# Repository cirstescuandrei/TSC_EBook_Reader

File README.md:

# TSC_EBook_Reader

### Cîrstescu Andrei-Vlad 331CC

# Tabletă E-Paper ESP32-C6 – Documentație Hardware

## Descriere Generală

Această tabletă cu afișaj E-Paper este proiectată pentru consum redus de energie și uzabilitate extinsă. 
Se bazează pe ESP32-C6 și include funcționalități precum citire din microSD, senzori de mediu, RTC și 
interacțiune cu utilizatorul prin butoane tactile.

# BOM
| Components                                                                                                                                                                 	| Links                                                                                                                                                                         	|
|----------------------------------------------------------------------------------------------------------------------------------------------------------------------------	|-------------------------------------------------------------------------------------------------------------------------------------------------------------------------------	|
| BOOT_BUTTON, RESET_BUTTON, CANGE_BUTTON                                                                                                                                    	| https://industry.panasonic.com/global/en/products/control/switch/light-touch/number/evqpuj02k                                                                                 	|
| C1, C1_BAT, C1_BAT1, C1_BAT2, C2, C2_BAT, C4, C4_USB, C5, C6, C7, C8, C9, C10, C_DELAY,  EPD_C1, EPD_C2, EPD_C5, EPD_C6, EPD_C7, EPD_C8, EPD_C9, EPD_C10, EPD_C11, EPD_C12 	| https://componentsearchengine.com/part-view/CC0402MRX5R5BB106/YAGEO                                                                                                           	|
| C3                                                                                                                                                                         	| https://componentsearchengine.com/part-view/TCJB107M002R0055E/Kyocera%20AVX                                                                                                   	|
| C10_SUPERCAP                                                                                                                                                               	| https://www.snapeda.com/parts/CPH3225A/Seiko+Instruments/view-part/?ref=eda                                                                                                   	|
| CHG_LED                                                                                                                                                                    	| https://www.snapeda.com/parts/KP-1608SURCK/Kingbright/view-part/?ref=search&t=LED%200603                                                                                      	|
| D1                                                                                                                                                                         	| https://www.snapeda.com/parts/USBLC6-2SC6Y/STMicroelectronics/view-part/?ref=eda                                                                                              	|
| D2, D7                                                                                                                                                                     	| https://eu.mouser.com/ProductDetail/KYOCERA-AVX/SD0805S020S1R0?qs=jCA%252BPfw4LHbpkAoSnwrdjw%3D%3D                                                                            	|
| D3, D4, D5                                                                                                                                                                 	| https://www.snapeda.com/parts/MBR0530/Onsemi/view-part/?ref=eda                                                                                                               	|
| D6, D8, D9, D10, D11, D12                                                                                                                                                  	| https://www.snapeda.com/parts/PGB1010603MR/Littelfuse/view-part/?ref=eda                                                                                                      	|
| IC1                                                                                                                                                                        	| https://componentsearchengine.com/part-view/BD5229G-TR/ROHM%20Semiconductor                                                                                                   	|
| IC4                                                                                                                                                                        	| https://componentsearchengine.com/part-view/XC6220A331MR-G/Torex                                                                                                              	|
| J1                                                                                                                                                                         	| https://www.mouser.co.uk/ProductDetail/Hirose-Connector/FH34SRJ-24S-0.5SH99?qs=vcbW%252B4%252BSTIpKBl5ap9J8Fw%3D%3D                                                           	|
| J2                                                                                                                                                                         	| https://componentsearchengine.com/part-view/USB4110-GF-A/GCT%20(GLOBAL%20CONNECTOR%20TECHNOLOGY                                                                               	|
| J3                                                                                                                                                                         	| https://www.mouser.co.uk/ProductDetail/Adafruit/4208?qs=PzGy0jfpSMtbScLbr0L5dw%3D%3D                                                                                          	|
| J4                                                                                                                                                                         	| https://store.comet.srl.ro/Catalogue/Product/43497/                                                                                                                           	|
| L1                                                                                                                                                                         	| https://eu.mouser.com/ProductDetail/Wurth-Elektronik/744043680?qs=PGXP4M47uW6VkZq%252BkzjrHA%3D%3D                                                                            	|
| PFMF.050.1                                                                                                                                                                 	| https://www.mouser.co.uk/ProductDetail/EPCOS-TDK/B72520T0350K062?qs=dEfas%2FXlABIszF52uu7vrg%3D%3D                                                                            	|
| Q1, Q2                                                                                                                                                                     	| https://componentsearchengine.com/part-view/DMG2305UX-7/Diodes%20Incorporated                                                                                                 	|
| Q3                                                                                                                                                                         	| https://componentsearchengine.com/part-view/SI1308EDL-T1-GE3/Vishay_                                                                                                         	|
| R1, R1-PINH, R1-PINH1, R1_BAT, R1_PWRUSB, R2, R2-PINH, R2-PINH1, R2-USB, R2-USB1, R2_BAT, R3, R4, R5, R6, R7, R8, R9, 10, R_BOOT, R_CAPACITOR, R_CHANGE, R_CL1, R_RESET    	| https://componentsearchengine.com/part-view/R0402%201%25%20100%20K%20(RC0402FR-07100KL)/YAGEO                                                                                 	|
| SENSOR2                                                                                                                                                                    	| https://www.snapeda.com/parts/BME680/Bosch/view-part/?welcome=home                                                                                                            	|
| SJ1                                                                                                                                                                        	| https://grabcad.com/library/solder-jumpers-1                                                                                                                                  	|
| TP                                                                                                                                                                         	| -                                                                                                                                                                             	|
| U1                                                                                                                                                                         	| https://www.snapeda.com/parts/W25Q512JVEIQ/Winbond+Electronics/view-part/?ref=eda                                                                                             	|
| U2                                                                                                                                                                         	| https://www.snapeda.com/parts/ESP32-C6-WROOM-1-N8/Espressif+Systems/view-part/?ref=eda                                                                                        	|
| U3                                                                                                                                                                         	| https://www.snapeda.com/parts/DS3231SN%23/Analog+Devices/view-part/?ref=eda                                                                                                   	|
| U4                                                                                                                                                                         	| https://www.snapeda.com/parts/MAX17048G+T10/Analog+Devices/view-part/?ref=eda                                                                                                 	|
| U5                                                                                                                                                                         	| https://www.mouser.co.uk/ProductDetail/Microchip-Technology/MCP73831T-5ACI-OT?qs=hH%252BOa0VZEiAcgAcEkuamXg%3D%3D 	|

---

## Componente Principale

### ESP32-C6-WROOM-1-N8
- Control total: afișaj, senzori, memorie
- Protocoale: SPI, I²C, UART, USB 2.0
- Consum: ~130 mA activ / ~12 µA deep sleep

### Afișaj E-Paper 7.5” (800x480 px)
- SPI + GPIO: BUSY, DC, RST, CS
- Consum 0 mA idle, ~26 mA la refresh
- Perfect pentru afișare statică de lungă durată

### Memorie
- **W25Q512 NOR Flash** (64MB, SPI) – firmware & cărți
- **MicroSD Card** (SPI partajat) – fișiere externe

### RTC – DS3231SN
- I²C + GPIO (INT, RST)
- Timp real precis, funcțional și în sleep
- Suportă trezirea automată

### Senzor Ambiental – BME680
- Temperatură, umiditate, presiune, compuși volatili
- I²C partajat cu RTC
- Consum redus: ~2.1 mA activ

### Alimentare
- **Baterie Li-Po 2500 mAh**
- **Încărcare USB-C** cu MCP73831 (max 1A)
- **LDO XC6220** – 3.3V stabil pentru sistem
- Monitorizare baterie prin MAX17048 (ADC pe IO18)
- LED încărcare controlat de IO4

### USB-C & Protecție
- Protocol: USB 2.0 + VBUS
- Programare + alimentare
- Protecție ESD integrată

### Interfață Utilizator
- 3 butoane tactile: BOOT (IO15), RESET (IO3), CHANGE (IO23)
- LED stare încărcare (IO4)

### Extensii
- **Qwiic/Stemma QT**: senzori I²C plug & play (IO19/IO20)
- GPIO suplimentari disponibili

---

## Pinout ESP32-C6

| Pin ESP32 | Funcție       | Periferic           |
|-----------|---------------|---------------------|
| IO2       | MISO (SPI)    | Flash, SD, E-Paper  |
| IO6       | SCK (SPI)     | Flash, SD, E-Paper  |
| IO7       | MOSI (SPI)    | Flash, SD, E-Paper  |
| IO12      | CS Flash      | Memorie NOR         |
| IO10      | CS E-Paper    | Display             |
| IO4       | CS SD         | microSD             |
| IO5       | DC E-Paper    | Display             |
| IO14      | BUSY E-Paper  | Display             |
| IO21      | RST E-Paper   | Display             |
| IO19/20   | SDA/SCL (I²C) | RTC, BME680, Qwiic  |
| IO0       | INT RTC       | RTC Wake            |
| IO17      | RTC RST       | RTC Reset           |
| IO18      | ADC Battery   | Monitorizare        |
| IO15      | BOOT          | Buton BOOT          |
| IO3       | RESET         | Buton RESET         |
| IO23      | CHANGE        | Buton navigare      |
| IO25/24   | UART TX/RX    | Debug Serial        |

---

## Estimare Consum

| Modul             | Activ           | Idle / Sleep     |
|------------------|------------------|------------------|
| ESP32-C6         | ~130 mA          | ~12 µA           |
| E-Paper          | ~26 mA           | 0 mA             |
| BME680           | ~2.1 mA          | 0.15 mA          |
| microSD          | 30–100 mA        | ~0.1 mA          |
| RTC              | ~1 µA            | -                |
| LED              | max 10 mA        | -                |

### Durată estimată cu baterie 2500 mAh
- Utilizare activă: **8–10 ore**
- Standby / Deep sleep: **până la 300 zile**

---

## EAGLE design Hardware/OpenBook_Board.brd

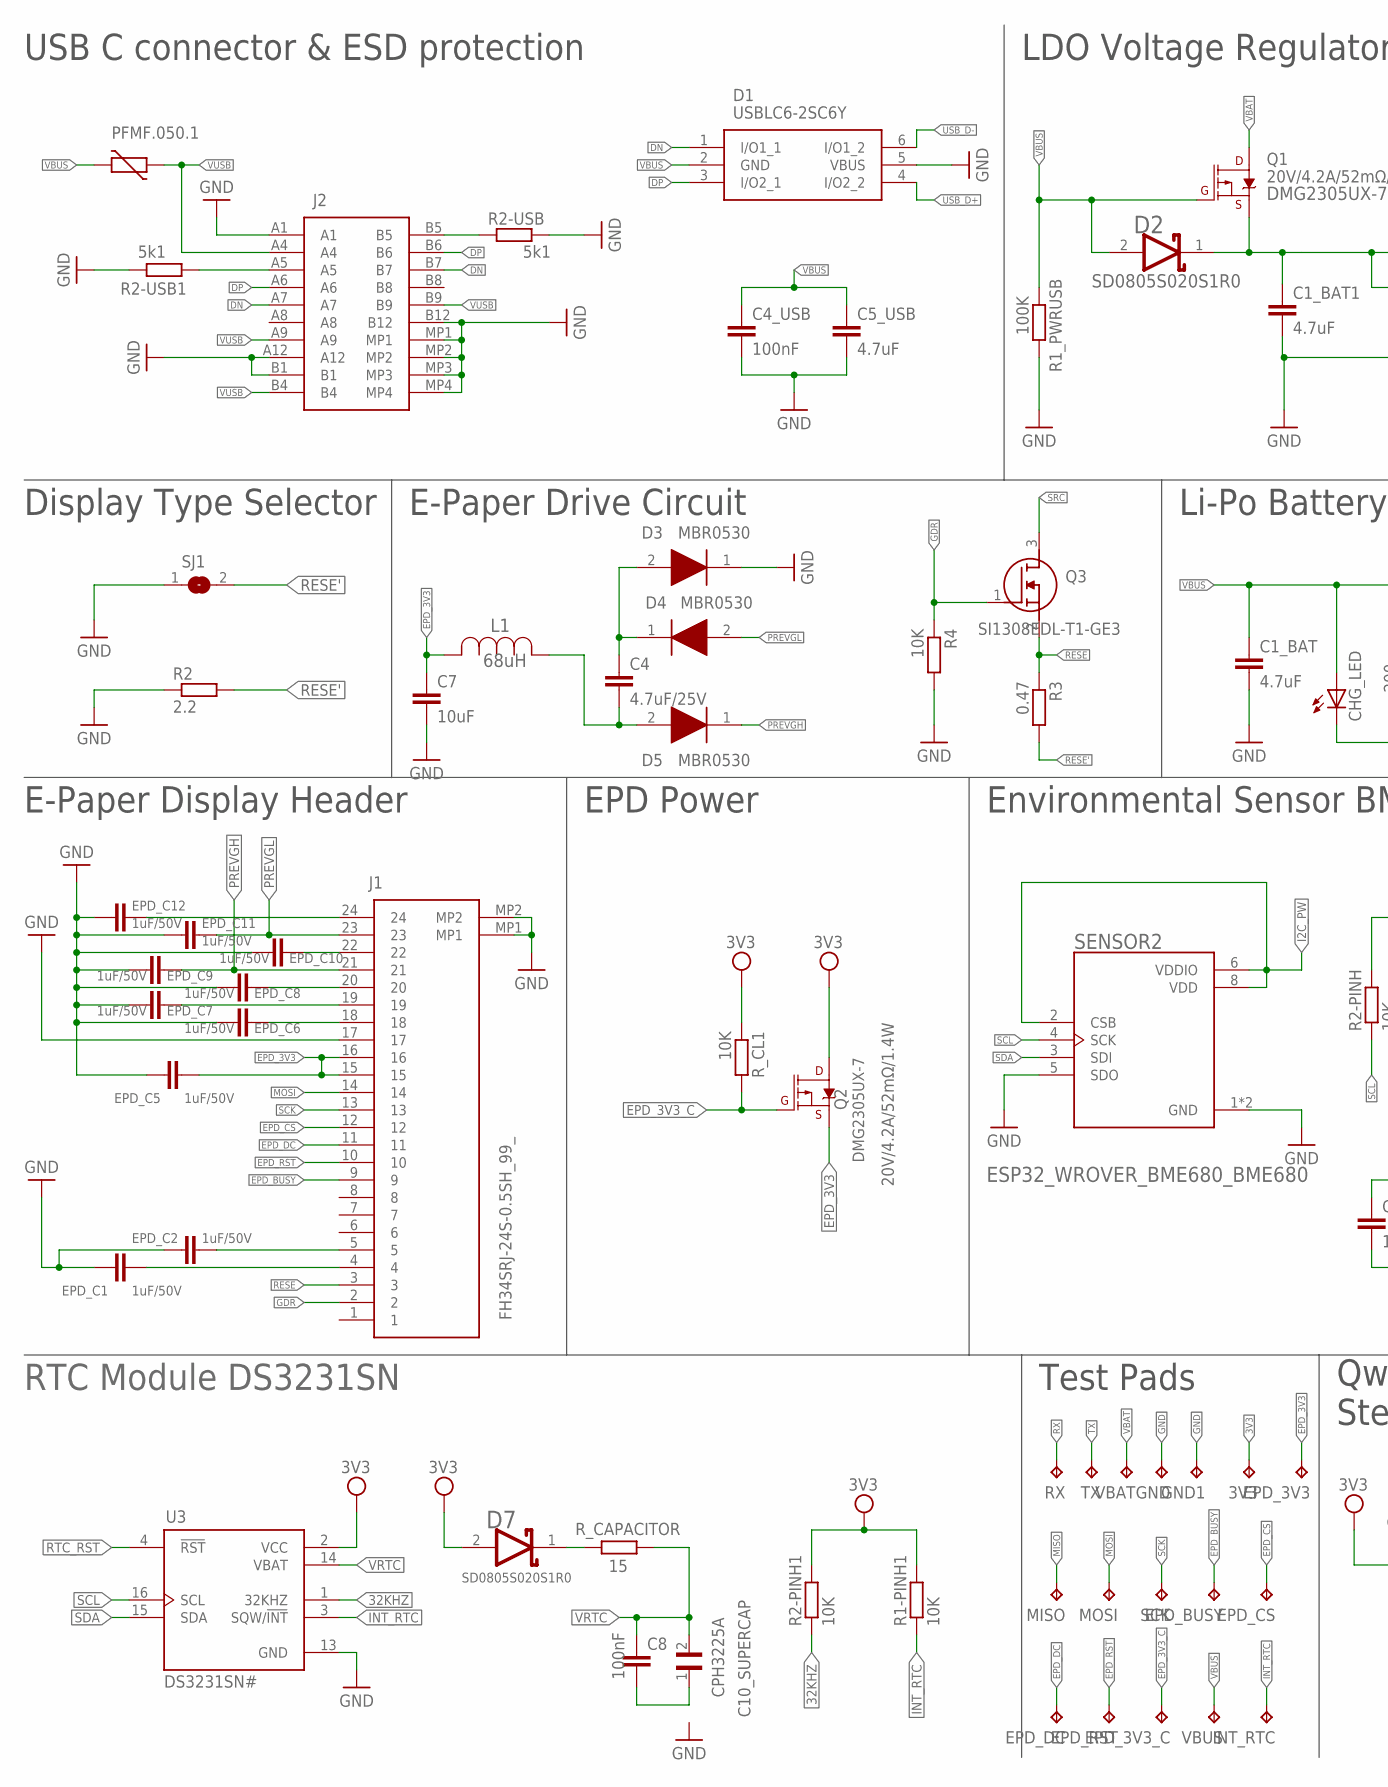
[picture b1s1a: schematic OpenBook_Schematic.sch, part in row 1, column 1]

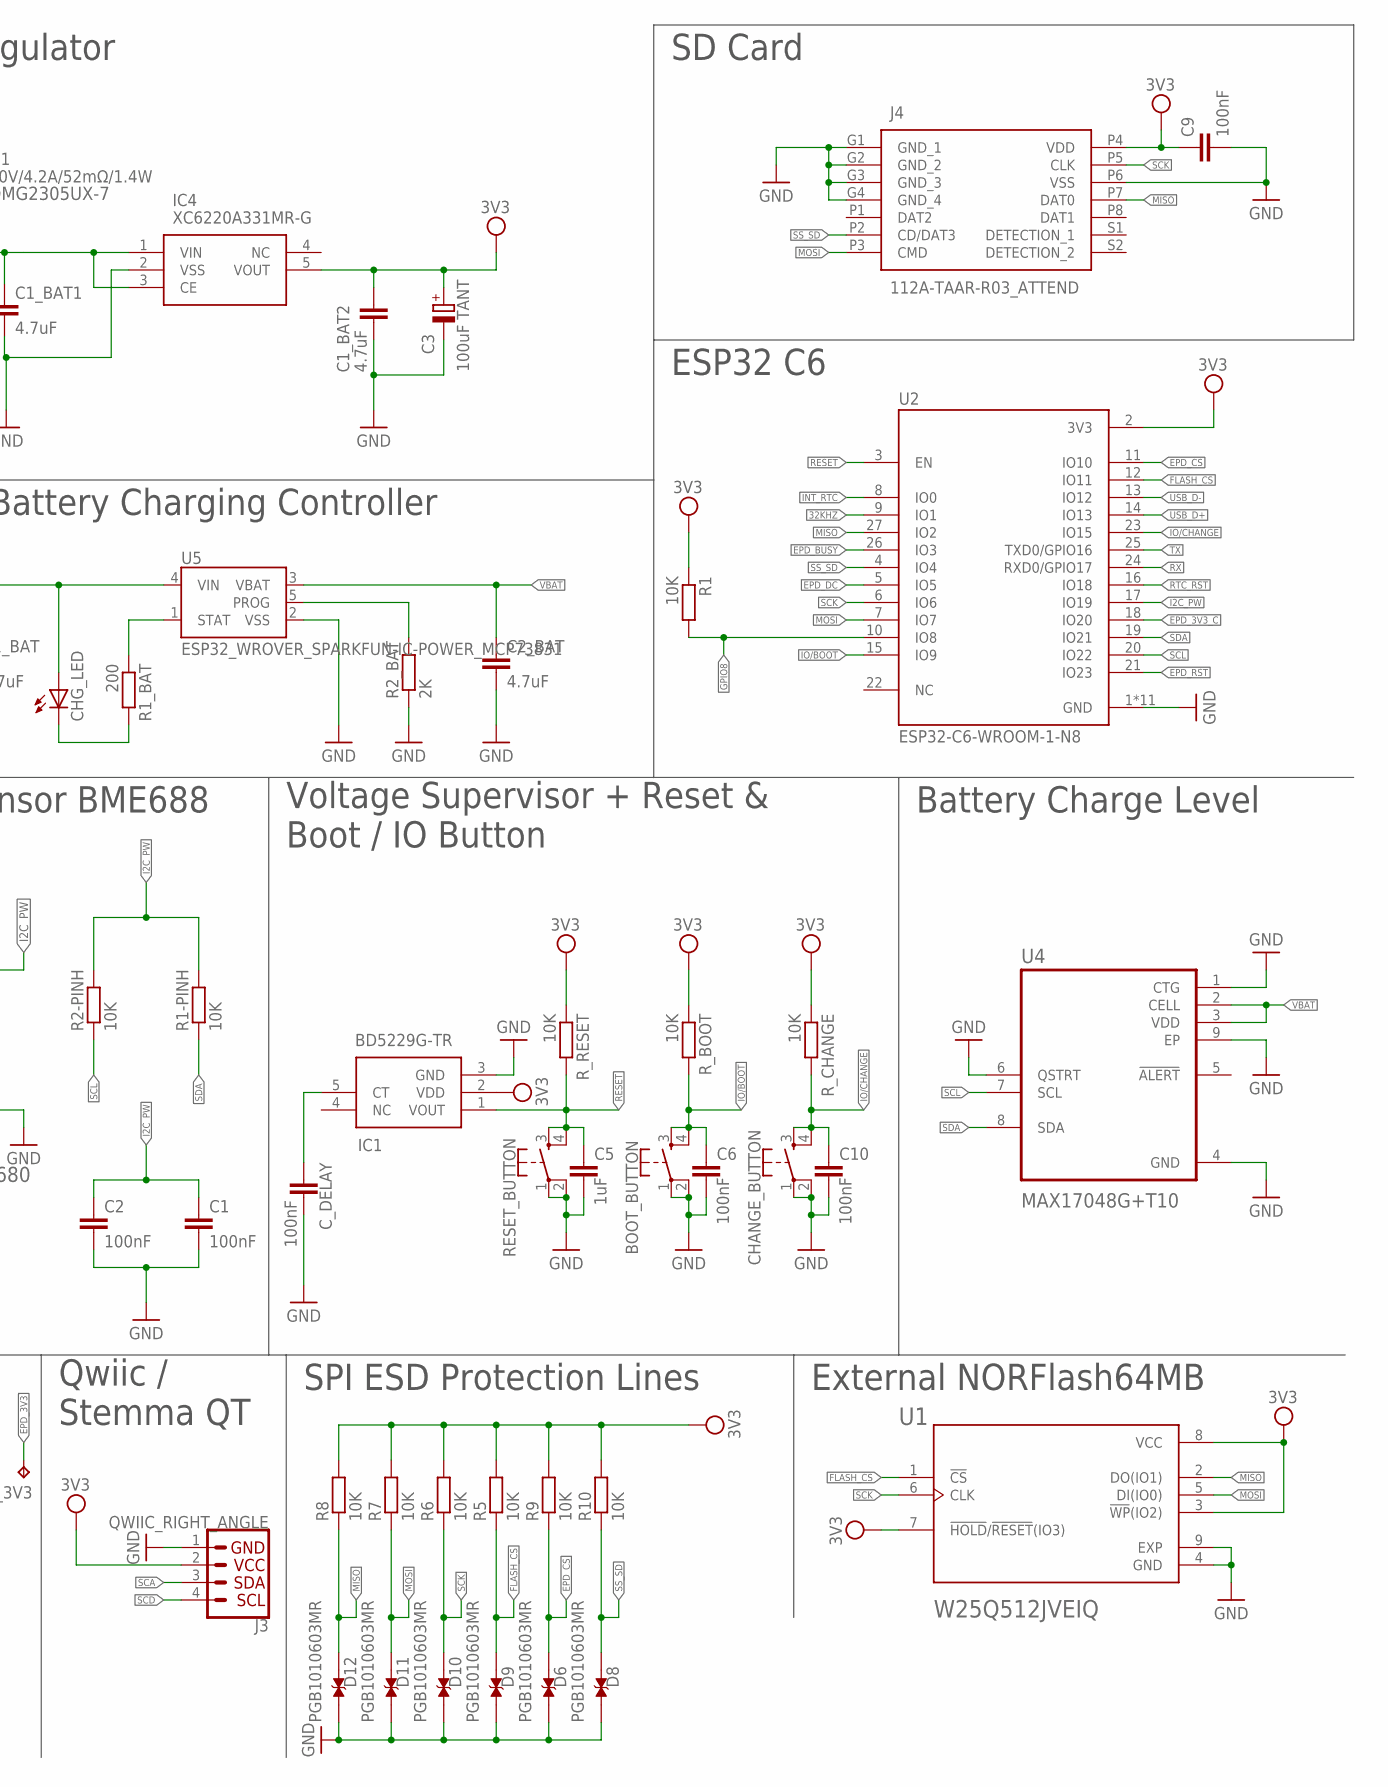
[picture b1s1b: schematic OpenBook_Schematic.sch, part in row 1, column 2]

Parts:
3V3: TPTP20R; TP20R
BOOT_BUTTON: BUTTON_CUSYOMV1BUTTON; MYBUTTON
C1, C2, C9: 100nF; ESP32_WROVER_EAGLE-LTSPICE_C0402
C1_BAT, C1_BAT1, C1_BAT2, C2_BAT, C5_USB: 4.7uF; EAGLE-LTSPICE_C0402
C3: 100uF TANT; RCL_CT3528
C4: 4.7uF/25V; EAGLE-LTSPICE_C0402
C4_USB, C6, C8, C10: 100nF; EAGLE-LTSPICE_C0402
C5: 1uF; EAGLE-LTSPICE_C0402
C7: 10uF; EAGLE-LTSPICE_C0402
C10_SUPERCAP: CPH3225A; CAPCP3225X100N
CHANGE_BUTTON: BUTTON_CUSYOMV1BUTTON; MYBUTTON
CHG_LED: ADAFRUIT_LEDCHIP-LED0603; ADAFRUIT_CHIP-LED0603
C_DELAY: 100nF; ESP32_WROVER_EAGLE-LTSPICE_C0402
D1: USBLC6-2SC6Y; SOT95P280X145-6N
D2, D7: ESP32_WROVER_AVX---SD0805S020S1R0_AVX_SD0805S020S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; ESP32_WROVER_AVX---SD0805S020S1R0_AVX_SD0805S020S1R0_0
D3, D4, D5: MBR0530; SOD3716X135N
D6, D8, D9, D10, D11, D12: PGB1010603MR; DIOC1608X36N
EPD_3V3, EPD_3V3_C: TPTP20R; TP20R
EPD_BUSY: TPTP20R; TP20R
EPD_C1, EPD_C2, EPD_C5, EPD_C6, EPD_C7, EPD_C8, EPD_C9, EPD_C10, EPD_C11, EPD_C12: 1uF/50V; ESP32_WROVER_EAGLE-LTSPICE_C0402
EPD_CS: TPTP20R; TP20R
EPD_DC: TPTP20R; TP20R
EPD_RST: TPTP20R; TP20R
GND, GND1: TPTP20R; TP20R
IC1: BD5229G-TR; SOT95P280X125-5N
IC4: XC6220A331MR-G; SOT95P280X120-5N
INT_RTC: TPTP20R; TP20R
J1: FH34SRJ-24S-0.5SH_99_; FH34SRJ24S05SH99
J2: SAMACSYS_PARTS_USB4110-GF-A; SAMACSYS_PARTS_USB4110GFA
J3: QWIIC_RIGHT_ANGLE; JST04_1MM_RA
J4: 112A-TAAR-R03_ATTEND; 112ATAARR03ATTEND
L1: 68uH; IND_4828-WE-TPC_WRE
MISO: TPTP20R; TP20R
MOSI: TPTP20R; TP20R
PFMF.050.1: ESP32C6_VARISTORCN1812; ESP32C6_VARISTOR_CT/CN1812
Q1, Q2: 20V/4.2A/52mΩ/1.4W; ESP32_WROVER_SPARKFUN-DISCRETESEMI_SOT23-3
Q3: SI1308EDL-T1-GE3; SOT65P210X110-3N
R1, R1-PINH, R1-PINH1, R2-PINH, R2-PINH1, R4, R5, R6, R7, R8, R9, R10: 10K; ESP32_WROVER_EAGLE-LTSPICE_R0402
R1_BAT: 200; ESP32_WROVER_EAGLE-LTSPICE_R0402
R1_PWRUSB: 100K; ESP32_WROVER_EAGLE-LTSPICE_R0402
R2: 2.2; ESP32_WROVER_EAGLE-LTSPICE_R0402
R2-USB, R2-USB1: 5k1; ESP32_WROVER_EAGLE-LTSPICE_R0402
R2_BAT: 2K; ESP32_WROVER_EAGLE-LTSPICE_R0402
R3: 0.47; ESP32_WROVER_EAGLE-LTSPICE_R0402
RESET_BUTTON: BUTTON_CUSYOMV1BUTTON; MYBUTTON
RX: TPTP20R; TP20R
R_BOOT: 10K; ESP32_WROVER_EAGLE-LTSPICE_R0402
R_CAPACITOR: 15; ESP32_WROVER_EAGLE-LTSPICE_R0402
R_CHANGE: 10K; ESP32_WROVER_EAGLE-LTSPICE_R0402
R_CL1: 10K; ESP32_WROVER_EAGLE-LTSPICE_R0402
R_RESET: 10K; ESP32_WROVER_EAGLE-LTSPICE_R0402
SCK: TPTP20R; TP20R
SENSOR2: ESP32_WROVER_BME680_BME680; ESP32_WROVER_BME680_PSON80P300X300X100-8N
SJ1: SJ
TX: TPTP20R; TP20R
U1: W25Q512JVEIQ; SON127P600X800X80-9N
U2: ESP32-C6-WROOM-1-N8; XCVR_ESP32-C6-WROOM-1-N8
U3: DS3231SN#; SOIC127P1032X265-16N
U4: MAX17048G+T10; SON50P200X200X80-9N
U5: ESP32_WROVER_SPARKFUN-IC-POWER_MCP73831; ESP32_WROVER_SPARKFUN-IC-POWER_SOT23-5
VBAT: TPTP20R; TP20R
VBUS: TPTP20R; TP20R

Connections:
3V3: 3V3.TP, C1_BAT2.1, C3.+, C9.1, D7.2 (ANODE), IC1.2 (VDD), IC4.5 (VOUT), J3.2, J4.P4 (VDD), Q2.3 (D), R1.1, R1-PINH1.2, R2-PINH1.2, R5.2, R6.2, R7.2, R8.2, R9.2, R10.2, R_BOOT.1, R_CHANGE.1, R_CL1.1, R_RESET.1, U1.3 (!WP!(IO2)), U1.7 (!HOLD!/!RESET!(IO3)), U1.8 (VCC), U2.2 (3V3), U3.2 (VCC)
32KHZ: R2-PINH1.1, U2.9 (IO1), U3.1 (32KHZ)
DN: D1.1 (I/O1_1), J2.A7, J2.B7
DP: D1.3 (I/O2_1), J2.A6, J2.B6
EPD_3V3: C7.1, EPD_3V3.TP, EPD_C5.1, J1.15, J1.16, L1.2, Q2.2 (S)
EPD_3V3_C: EPD_3V3_C.TP, Q2.1 (G), R_CL1.2, U2.18 (IO20)
EPD_BUSY: EPD_BUSY.TP, J1.9, U2.26 (IO3)
EPD_CS: D6.2, EPD_CS.TP, J1.12, R9.1, U2.11 (IO10)
EPD_DC: EPD_DC.TP, J1.11, U2.5 (IO5)
EPD_RST: EPD_RST.TP, J1.10, U2.21 (IO23)
FLASH_CS: D9.2, R5.1, U1.1 (!CS), U2.12 (IO11)
GDR: J1.2, Q3.1 (G), R4.1
GND: BOOT_BUTTON.1, BOOT_BUTTON.2, C1.2, C1_BAT.2, C1_BAT1.2, C1_BAT2.2, C2.2, C2_BAT.2, C3.-, C4_USB.2, C5.2, C5_USB.2, C6.2, C7.2, C9.2, C10.2, CHANGE_BUTTON.1, CHANGE_BUTTON.2, C_DELAY.2, D1.5 (VBUS), D3.1 (K), D6.1, D8.1, D9.1, D10.1, D11.1, D12.1, EPD_C1.2, EPD_C2.2, EPD_C5.2, EPD_C6.2, EPD_C7.2, EPD_C8.2, EPD_C9.2, EPD_C10.2, EPD_C11.2, EPD_C12.2, GND.TP, GND1.TP, IC1.3 (GND), IC4.2 (VSS), J1.17, J1.MP1, J1.MP2, J2.A1, J2.A12, J2.B1, J2.B12, J2.MP1, J2.MP2, J2.MP3, J2.MP4, J3.1, J4.G1 (GND_1), J4.G2 (GND_2), J4.G3 (GND_3), J4.G4 (GND_4), J4.P6 (VSS), R1_PWRUSB.2, R2.1, R2-USB.2, R2-USB1.1, R2_BAT.1, R4.2, RESET_BUTTON.1, RESET_BUTTON.2, SENSOR2.1 (GND), SENSOR2.5 (SDO), SENSOR2.7 (GND), SJ1.1, U1.4 (GND), U1.9 (EXP), U2.1 (GND), U2.28 (GND), U2.29_1 (GND), U2.29_2 (GND), U2.29_3 (GND), U2.29_4 (GND), U2.29_5 (GND), U2.29_6 (GND), U2.29_7 (GND), U2.29_8 (GND), U2.29_9 (GND), U3.13 (GND), U4.1 (CTG), U4.4 (GND), U4.6 (QSTRT), U4.9 (EP), U5.2 (VSS)
GPIO8: R1.2, U2.10 (IO8)
I2C_PW: C1.1, C2.1, R1-PINH.2, R2-PINH.2, SENSOR2.2 (CSB), SENSOR2.6 (VDDIO), SENSOR2.8 (VDD), U2.17 (IO19)
INT_RTC: INT_RTC.TP, R1-PINH1.1, U2.8 (IO0), U3.3 (SQW/!INT)
IO/BOOT: BOOT_BUTTON.3, BOOT_BUTTON.4, C6.1, R_BOOT.2, U2.15 (IO9)
IO/CHANGE: C10.1, CHANGE_BUTTON.3, CHANGE_BUTTON.4, R_CHANGE.2, U2.23 (IO15)
MISO: D12.2, J4.P7 (DAT0), MISO.TP, R8.1, U1.2 (DO(IO1)), U2.27 (IO2)
MOSI: D11.2, J1.14, J4.P3 (CMD), MOSI.TP, R7.1, U1.5 (DI(IO0)), U2.7 (IO7)
unnamed: D7.1 (CATHODE), R_CAPACITOR.2
unnamed: EPD_C2.1, J1.5
unnamed: C8.2, C10_SUPERCAP.1
unnamed: EPD_C1.1, J1.4
unnamed: EPD_C6.1, J1.18
unnamed: EPD_C7.1, J1.19
unnamed: C_DELAY.1, IC1.5 (CT)
unnamed: C4.2, D5.2 (A), L1.1
unnamed: EPD_C8.1, J1.20
unnamed: C4.1, D3.2 (A), D4.1 (K)
unnamed: EPD_C10.1, J1.22
unnamed: EPD_C12.1, J1.24
unnamed: CHG_LED.C, R1_BAT.2
unnamed: R1_BAT.1, U5.1 (STAT)
unnamed: R2_BAT.2, U5.5 (PROG)
unnamed: C1_BAT1.1, D2.1 (CATHODE), IC4.1 (VIN), IC4.3 (CE), Q1.2 (S)
unnamed: J2.A5, R2-USB1.2
unnamed: J2.B5, R2-USB.1
PREVGH: D5.1 (K), EPD_C9.1, J1.21
PREVGL: D4.2 (A), EPD_C11.1, J1.23
RESE: J1.3, Q3.2 (S), R3.1
RESE': R2.2, R3.2, SJ1.2
RESET: C5.1, IC1.1 (VOUT), RESET_BUTTON.3, RESET_BUTTON.4, R_RESET.2, U2.3 (EN)
RTC_RST: U2.16 (IO18), U3.4 (!RST)
RX: RX.TP, U2.24 (RXD0/GPIO17)
SCA: J3.3
SCD: J3.4
SCK: D10.2, J1.13, J4.P5 (CLK), R6.1, SCK.TP, U1.6 (CLK), U2.6 (IO6)
SCL: R2-PINH.1, SENSOR2.4 (SCK), U2.20 (IO22), U3.16 (SCL), U4.7 (SCL)
SDA: R1-PINH.1, SENSOR2.3 (SDI), U2.19 (IO21), U3.15 (SDA), U4.8 (SDA)
SRC: Q3.3 (D)
SS_SD: D8.2, J4.P2 (CD/DAT3), R10.1, U2.4 (IO4)
TX: TX.TP, U2.25 (TXD0/GPIO16)
USB_D+: D1.4 (I/O2_2), U2.14 (IO13)
USB_D-: D1.6 (I/O1_2), U2.13 (IO12)
VBAT: C2_BAT.1, Q1.3 (D), U4.2 (CELL), U4.3 (VDD), U5.3 (VBAT), VBAT.TP
VBUS: C1_BAT.1, C4_USB.1, C5_USB.1, CHG_LED.A, D1.2 (GND), D2.2 (ANODE), PFMF.050.1.2, Q1.1 (G), R1_PWRUSB.1, U5.4 (VIN), VBUS.TP
VRTC: C8.1, C10_SUPERCAP.2, R_CAPACITOR.1, U3.14 (VBAT)
VUSB: J2.A4, J2.A9, J2.B4, J2.B9, PFMF.050.1.1

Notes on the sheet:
SD0805S020S1R0
RTC Module DS3231SN
Test Pads
Qwiic / Stemma QT
SPI ESD Protection Lines
External NORFlash64MB
EPD Power
DMG2305UX-7
E-Paper Display Header
Environmental Sensor BME688
Voltage Supervisor + Reset & Boot / IO Button
Battery Charge Level
Display Type Selector
E-Paper Drive Circuit
Li-Po Battery Charging Controller
ESP32 C6
SD Card
LDO Voltage Regulator
USB C connector & ESD protection

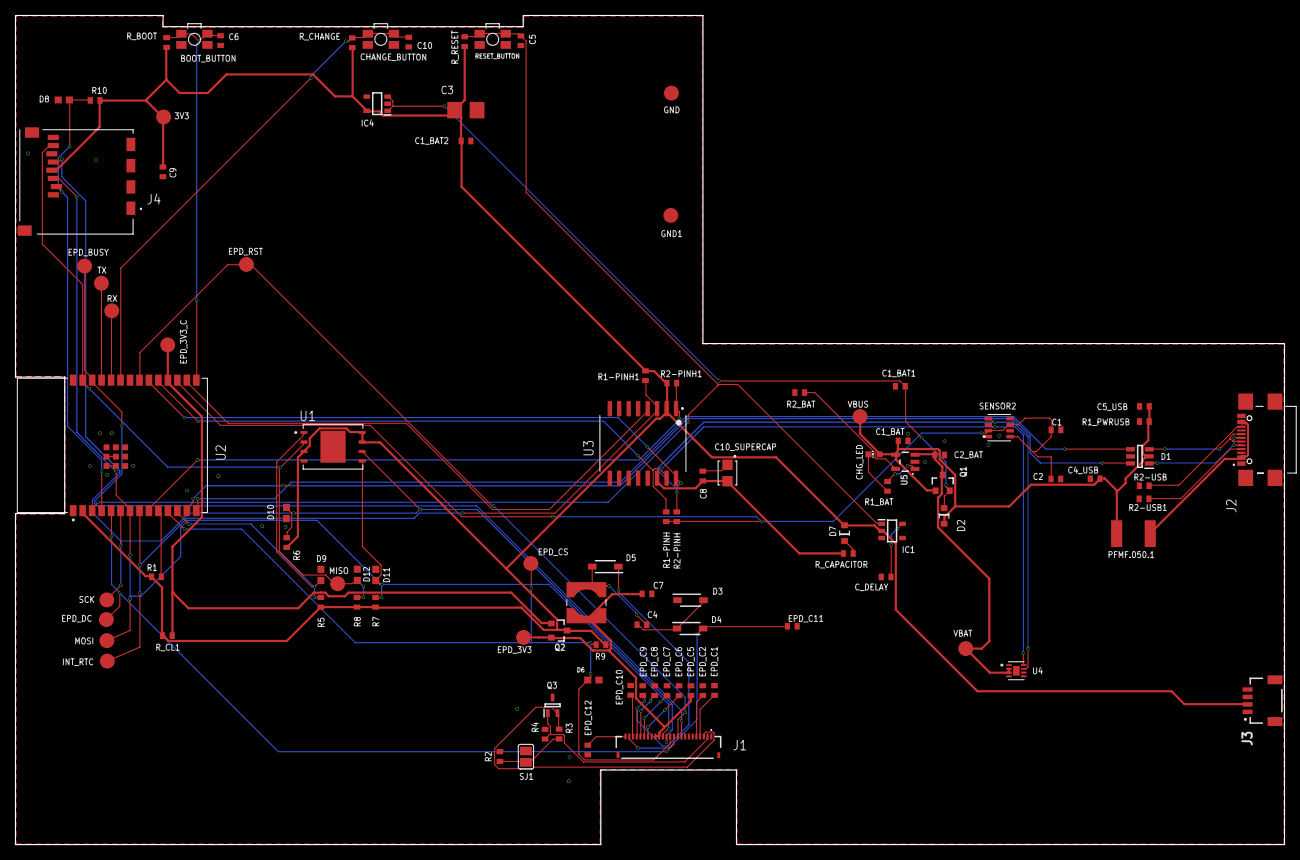
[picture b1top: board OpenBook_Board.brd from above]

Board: 2 copper layers, 170.2 x 111.2 mm, 103 parts (0 on the bottom side), 56 nets.

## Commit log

2025-04-05 Added Project Files
2025-04-05 Create LICENSE
2025-04-12 Added final Board
    Fixed measure layer issues, reduced PCB thickness to 1mm and removed unnecessary GND traces
2025-04-12 Added redone gerbers

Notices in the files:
parts and their libraries:
COPYRIGHT: Copyright (C) 2024 Ultra Librarian. All rights reserved.
